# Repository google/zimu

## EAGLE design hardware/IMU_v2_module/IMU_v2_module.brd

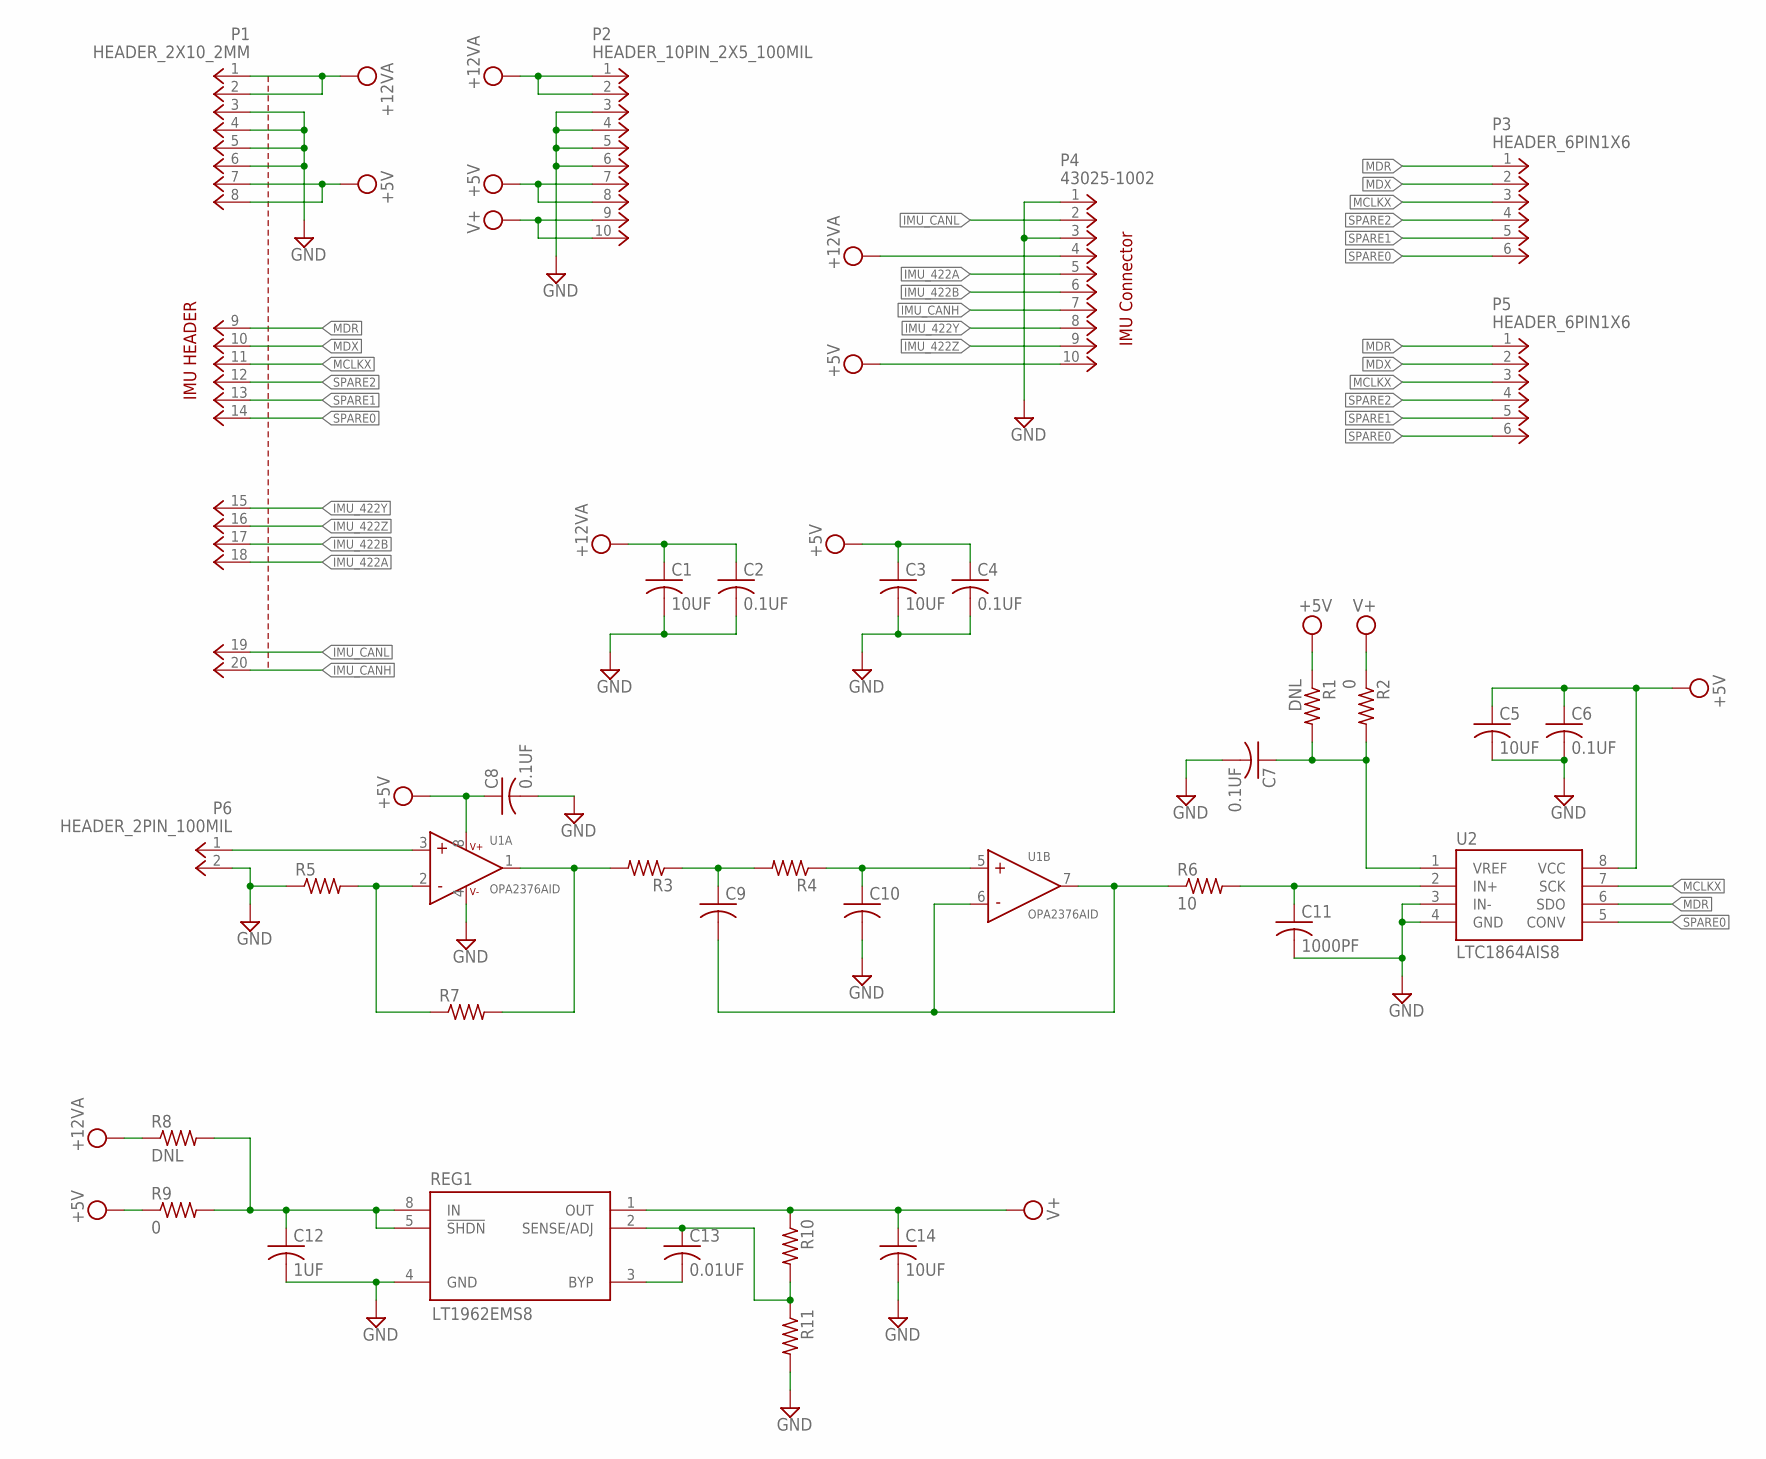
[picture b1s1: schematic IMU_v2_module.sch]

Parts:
C1, C3, C14: 10UF; C1206K
C2, C4, C6, C7, C8: 0.1UF; C0603K
C5: 10UF; C1206
C9, C10: C0603K
C11: 1000PF; C0603K
C12: 1UF; C0603K
C13: 0.01UF; C0603K
P1: HEADER_2X10_2MM
P2: HEADER_10PIN_2X5_100MIL; HEADER_2X5
P3, P5: HEADER_6PIN1X6; HEADER_1X6
P4: 43025-1002; MICRO-FIT_10RA
P6: HEADER_2PIN_100MIL; HEADER_1X2
R1, R8: DNL; R0603
R2, R9: 0; R0603
R3, R4, R5, R7: R0603
R6: 10; R0603
R10, R11: R-US_R0603; R0603
REG1: LT1962EMS8; MSOP8
U1: OPA2376AID; SOIC8
U2: LTC1864AIS8; SOIC8

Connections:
+5V: C3.1, C4.1, C5.1, C6.1, C8.1, P1.7, P1.8, P2.7, P2.8, P4.10, R1.1, R9.1, U1.8 (V+), U2.8 (VCC)
+12VA: C1.1, C2.1, P1.1, P1.2, P2.1, P2.2, P4.4, R8.1
GND: C1.2, C2.2, C3.2, C4.2, C5.2, C6.2, C7.2, C8.2, C10.2, C11.2, C12.2, C14.2, P1.3, P1.4, P1.5, P1.6, P2.3, P2.4, P2.5, P2.6, P4.1, P4.3, P6.2, R5.1, R11.2, REG1.4 (GND), U1.4 (V-), U2.3 (IN-), U2.4 (GND)
IMU_422A: P1.18, P4.5
IMU_422B: P1.17, P4.6
IMU_422Y: P1.15, P4.8
IMU_422Z: P1.16, P4.9
IMU_CANH: P1.20, P4.7
IMU_CANL: P1.19, P4.2
LC_A: C9.2, R6.1, U1.6 (IN-), U1.7 (OUT)
MCLKX: P1.11, P3.3, P5.3, U2.7 (SCK)
MDR: P1.9, P3.1, P5.1, U2.6 (SDO)
MDX: P1.10, P3.2, P5.2
unnamed: C12.1, R8.2, R9.2, REG1.5 (!SHDN), REG1.8 (IN)
unnamed: C7.1, R1.2, R2.2, U2.1 (VREF)
unnamed: R5.2, R7.1, U1.2 (IN-)
unnamed: P6.1, U1.3 (IN+)
unnamed: R3.2, R7.2, U1.1 (OUT)
unnamed: C11.1, R6.2, U2.2 (IN+)
unnamed: C9.1, R3.1, R4.2
unnamed: C10.1, R4.1, U1.5 (IN+)
unnamed: C13.2, REG1.3 (BYP)
unnamed: C13.1, R10.2, R11.1, REG1.2 (SENSE/ADJ)
SPARE0: P1.14, P3.6, P5.6, U2.5 (CONV)
SPARE1: P1.13, P3.5, P5.5
SPARE2: P1.12, P3.4, P5.4
V+: C14.1, P2.9, P2.10, R2.1, R10.1, REG1.1 (OUT)

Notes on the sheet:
IMU HEADER
IMU Connector

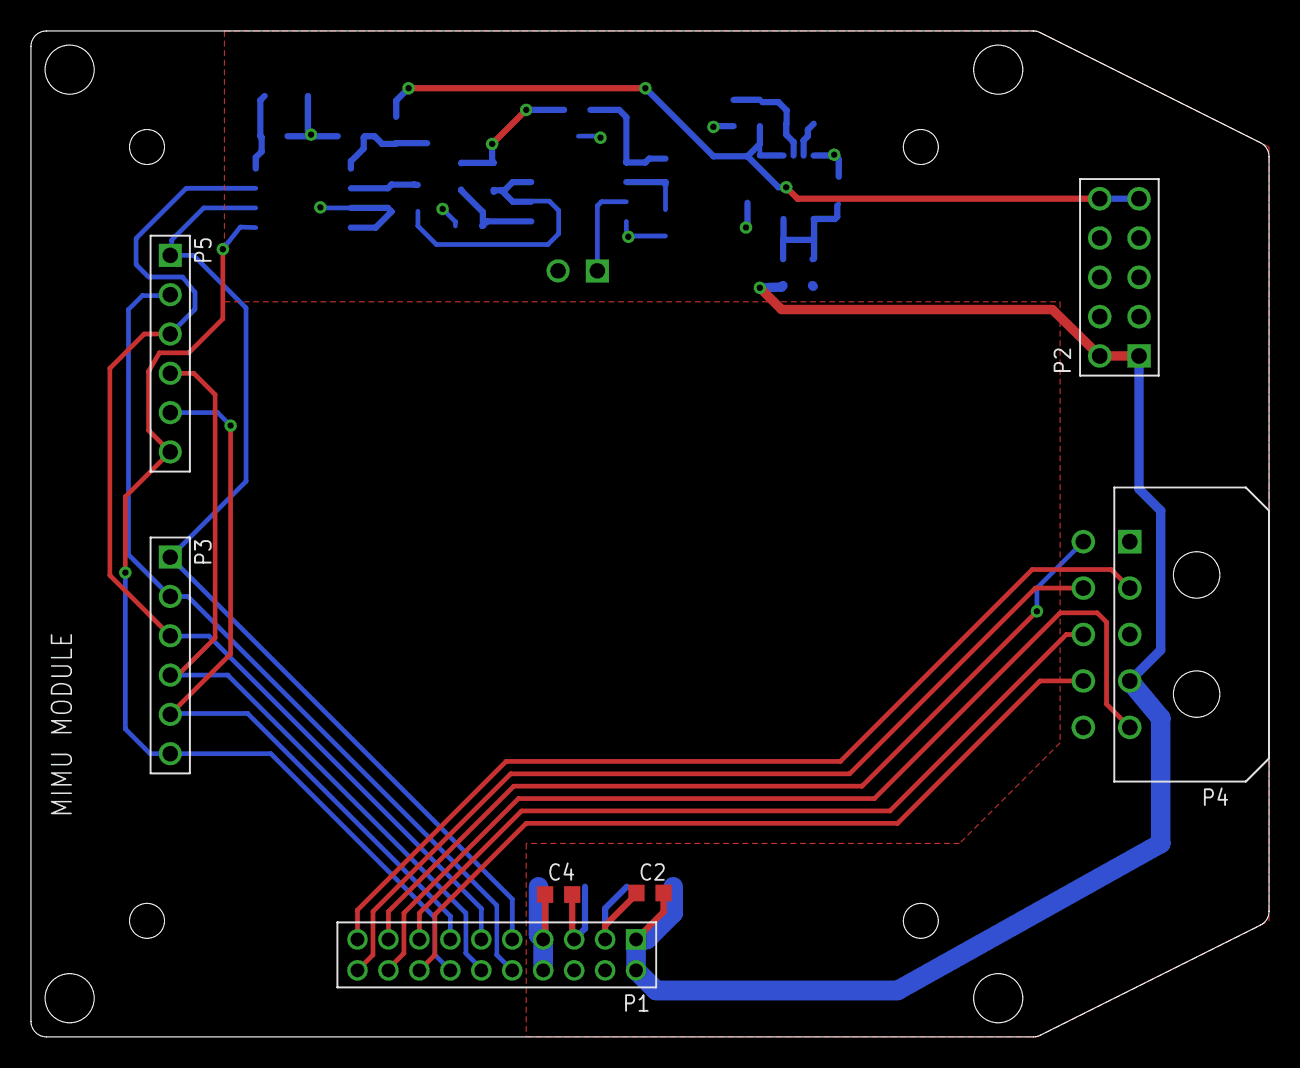
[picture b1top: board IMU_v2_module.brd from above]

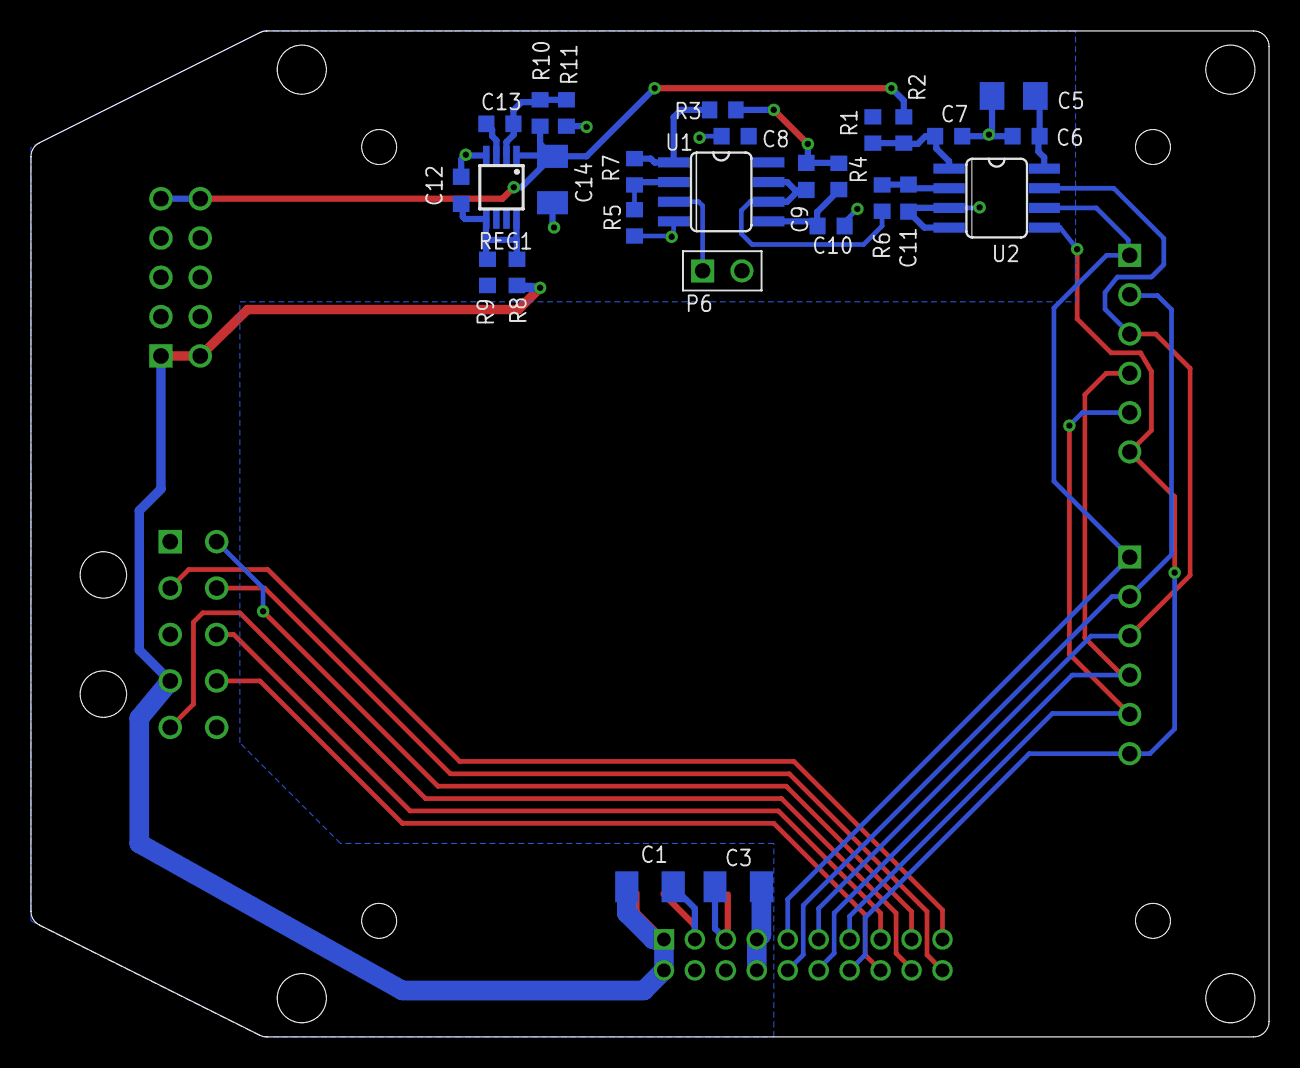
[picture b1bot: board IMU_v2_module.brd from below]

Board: 2 copper layers, 80.0 x 65.0 mm, 34 parts (27 on the bottom side), 27 nets.

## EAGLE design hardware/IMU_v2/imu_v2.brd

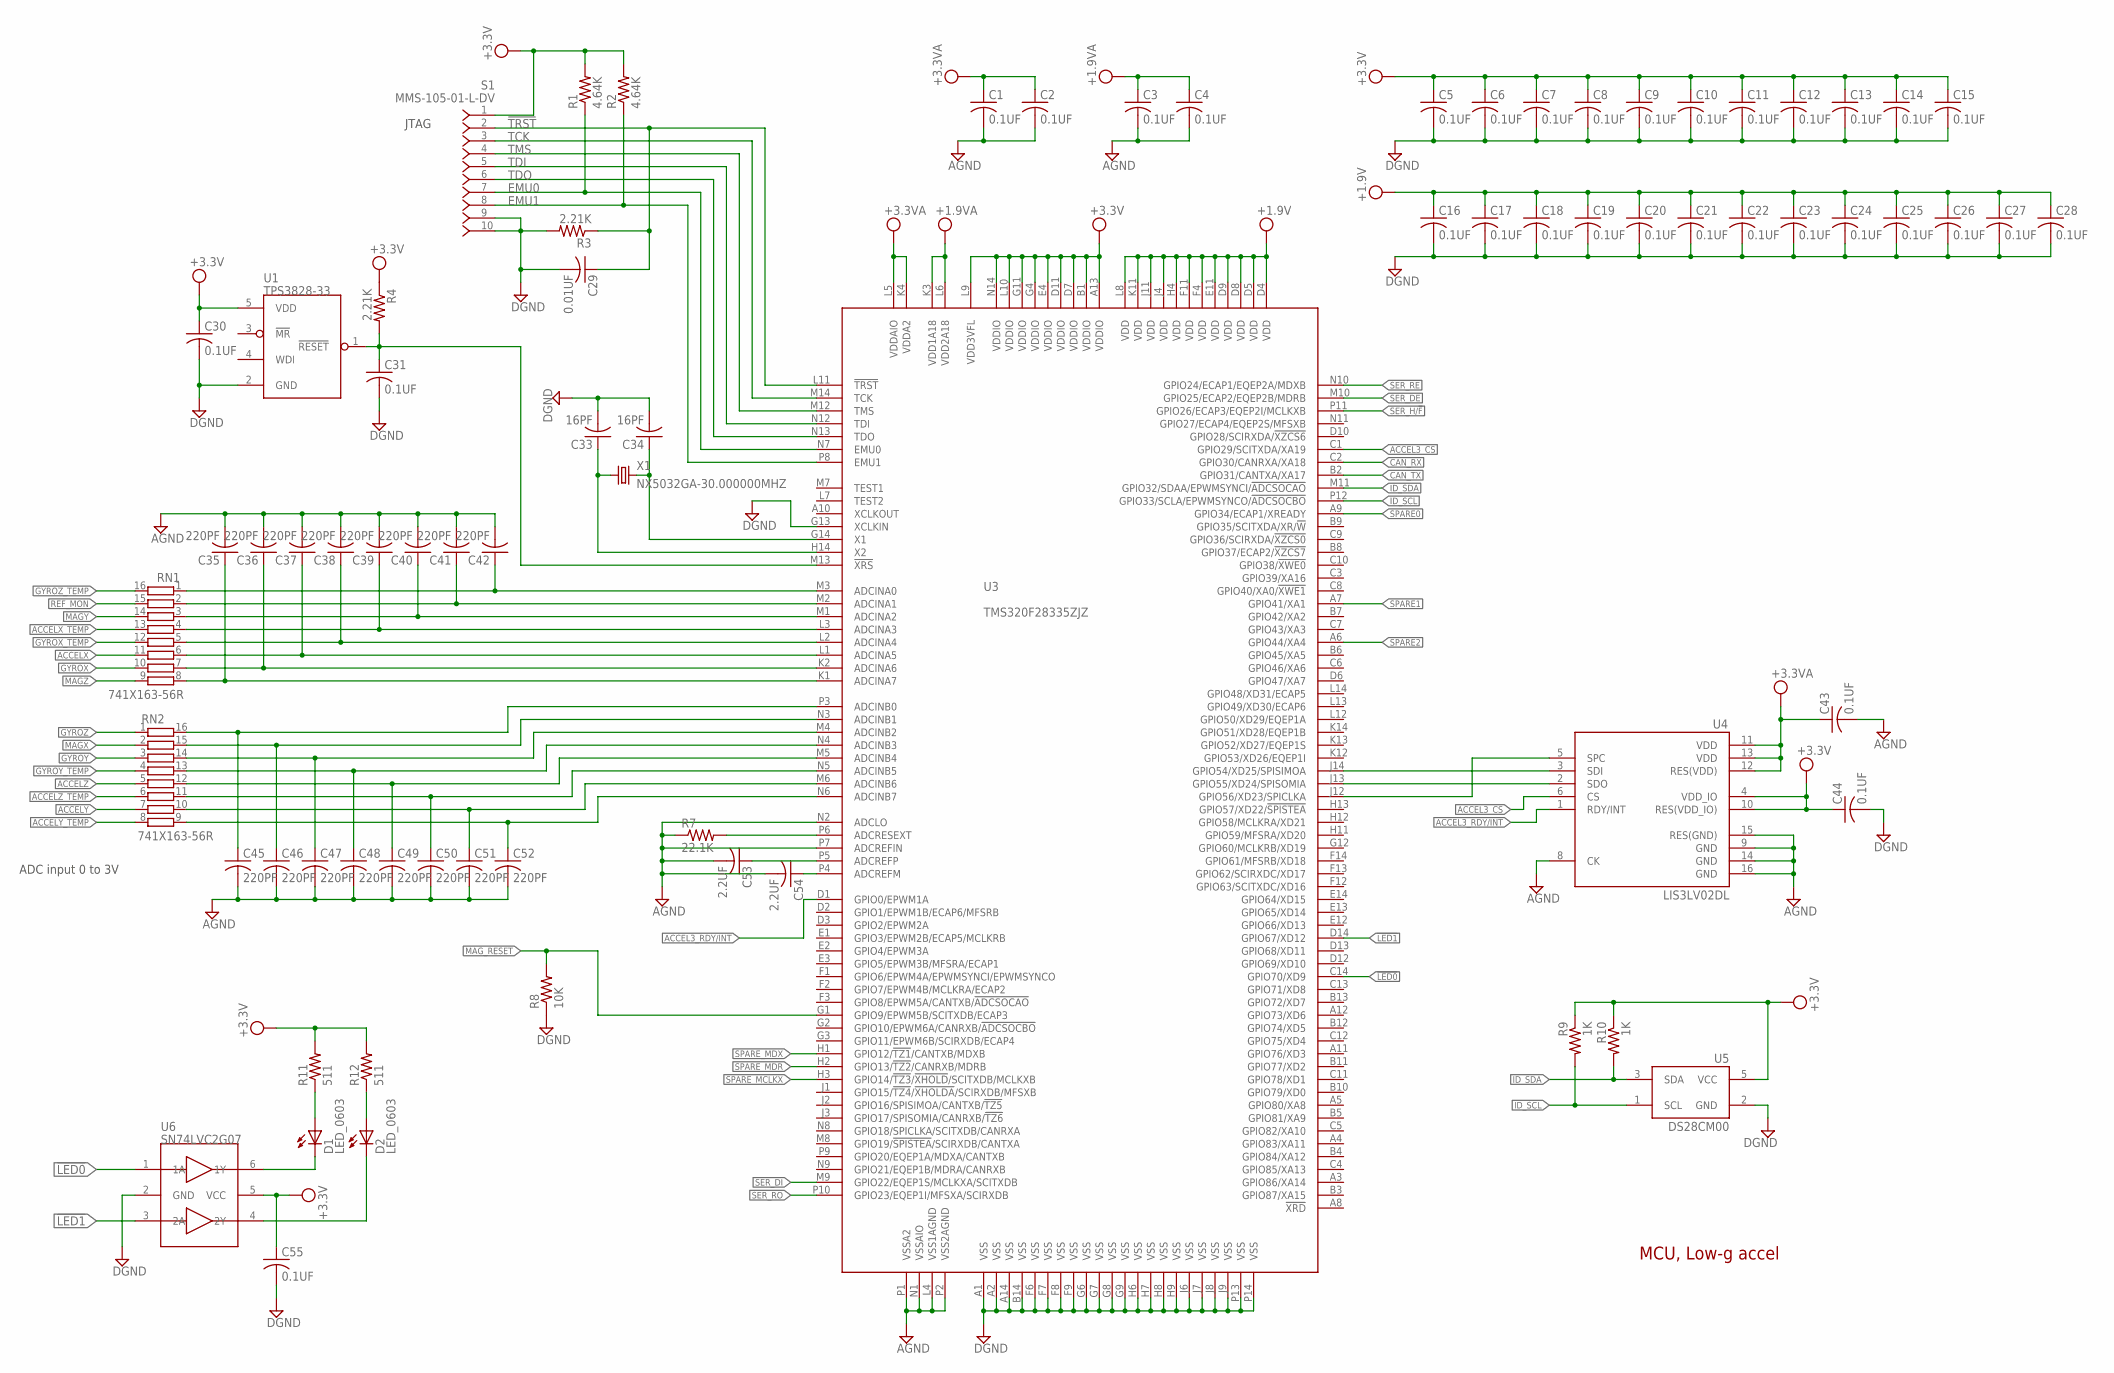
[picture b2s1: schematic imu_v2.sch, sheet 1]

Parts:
C1, C2, C3, C4, C5, C6, C7, C8, C9, C10, C11, C12, C13, C14, C15, C16, C17, C18, C19, C20, C21, C22, C23, C24, C25, C26, C27, C28, C30, C31, C43, C44, C55: 0.1UF; C0603K
C29: 0.01UF; C0603K
C33, C34: 16PF; C0603K
C35, C36, C37, C38, C39, C40, C41, C42, C45, C46, C47, C48, C49, C50, C51, C52: 220PF; C0603K
C53, C54: 2.2UF; C0603K
D1, D2: LED_0603
R1, R2: 4.64K; R0603
R3, R4: 2.21K; R0603
R7: 22.1K; R0603
R8: 10K; R0603
R9, R10: 1K; R0603
R11, R12: 511; R0603
RN1, RN2: 741X163-56R; 741X163
S1: MMS-105-01-L-DV; HEADER_2X5_2MM_TH
U1: TPS3828-33; SOT23-5
U3: TMS320F28335ZJZ; ZJZ_PBGA176
U4: LIS3LV02DL; LIS3LV02DL_LGA16
U5: DS28CM00; SOT23-5L
U6: SN74LVC2G07; SOT23-6
X1: NX5032GA-30.000000MHZ; NX5032GA

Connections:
!LED0: U3.C14 (GPIO70/XD9), U6.1 (1A)
!LED1: U3.D14 (GPIO67/XD12), U6.3 (2A)
!TRST: C29.1, R3.1, S1.2 (1), U3.L11 (!TRST!)
+1.9V: C16.1, C17.1, C18.1, C19.1, C20.1, C21.1, C22.1, C23.1, C24.1, C25.1, C26.1, C27.1, C28.1, U3.D4 (VDD), U3.D5 (VDD), U3.D8 (VDD), U3.D9 (VDD), U3.E11 (VDD), U3.F4 (VDD), U3.F11 (VDD), U3.H4 (VDD), U3.J4 (VDD), U3.J11 (VDD), U3.K11 (VDD), U3.L8 (VDD); also elsewhere on the board
+1.9VA: C3.1, C4.1, U3.K3 (VDD1A18), U3.L6 (VDD2A18); also elsewhere on the board
+3.3V: C5.1, C6.1, C7.1, C8.1, C9.1, C10.1, C11.1, C12.1, C13.1, C14.1, C15.1, C30.1, C44.1, C55.1, R1.2, R2.2, R4.1, R9.1, R10.1, R11.2, R12.2, S1.1, U1.5 (VDD), U3.A13 (VDDIO), U3.B1 (VDDIO), U3.D7 (VDDIO), U3.D11 (VDDIO), U3.E4 (VDDIO), U3.G4 (VDDIO), U3.G11 (VDDIO), U3.L9 (VDD3VFL), U3.L10 (VDDIO), U3.N14 (VDDIO), U4.4 (VDD_IO), U4.10 (RES(VDD_IO)), U5.5 (VCC), U6.5 (VCC); also elsewhere on the board
+3.3VA: C1.1, C2.1, C43.1, U3.K4 (VDDA2), U3.L5 (VDDAIO), U4.11 (VDD), U4.12 (RES(VDD)), U4.13 (VDD); also elsewhere on the board
ACCEL3_CLK: U3.J12 (GPIO56/XD23/SPICLKA), U4.5 (SPC)
ACCEL3_CS: U3.C1 (GPIO29/SCITXDA/XA19), U4.6 (CS)
ACCEL3_RDY/INT: U3.D1 (GPIO0/EPWM1A), U4.1 (RDY/INT)
ACCEL3_SIMO: U3.J14 (GPIO54/XD25/SPISIMOA), U4.3 (SDI)
ACCEL3_SOMI: U3.J13 (GPIO55/XD24/SPISOMIA), U4.2 (SDO)
ACCELX: RN1.11; also elsewhere on the board
ACCELX_TEMP: RN1.13; also elsewhere on the board
ACCELY: RN2.7; also elsewhere on the board
ACCELY_TEMP: RN2.8; also elsewhere on the board
ACCELZ: RN2.5; also elsewhere on the board
ACCELZ_TEMP: RN2.6; also elsewhere on the board
AGND: C1.2, C2.2, C3.2, C4.2, C35.2, C36.2, C37.2, C38.2, C39.2, C40.2, C41.2, C42.2, C43.2, C45.2, C46.2, C47.2, C48.2, C49.2, C50.2, C51.2, C52.2, C53.2, C54.2, R7.1, U3.L4 (VSS1AGND), U3.N1 (VSSAIO), U3.N2 (ADCLO), U3.P1 (VSSA2), U3.P2 (VSS2AGND), U3.P7 (ADCREFIN), U4.8 (CK), U4.9 (GND), U4.14 (GND), U4.15 (RES(GND)), U4.16 (GND); also elsewhere on the board
CAN_RX: U3.C2 (GPIO30/CANRXA/XA18); also elsewhere on the board
CAN_TX: U3.B2 (GPIO31/CANTXA/XA17); also elsewhere on the board
DGND: C5.2, C6.2, C7.2, C8.2, C9.2, C10.2, C11.2, C12.2, C13.2, C14.2, C15.2, C16.2, C17.2, C18.2, C19.2, C20.2, C21.2, C22.2, C23.2, C24.2, C25.2, C26.2, C27.2, C28.2, C29.2, C30.2, C31.2, C33.2, C34.2, C44.2, C55.2, R3.2, R8.1, S1.9 (1), S1.10 (1), U1.2 (GND), U3.A1 (VSS), U3.A2 (VSS), U3.A14 (VSS), U3.B14 (VSS), U3.F6 (VSS), U3.F7 (VSS), U3.F8 (VSS), U3.F9 (VSS), U3.G6 (VSS), U3.G7 (VSS), U3.G8 (VSS), U3.G9 (VSS), U3.G13 (XCLKIN), U3.H6 (VSS), U3.H7 (VSS), U3.H8 (VSS), U3.H9 (VSS), U3.J6 (VSS), U3.J7 (VSS), U3.J8 (VSS), U3.J9 (VSS), U3.P13 (VSS), U3.P14 (VSS), U5.2 (GND), U6.2 (GND); also elsewhere on the board
EMU0: R1.1, S1.7 (1), U3.N7 (EMU0)
EMU1: R2.1, S1.8 (1), U3.P8 (EMU1)
GYROX: RN1.10; also elsewhere on the board
GYROX_TEMP: RN1.12; also elsewhere on the board
GYROY: RN2.3; also elsewhere on the board
GYROY_TEMP: RN2.4; also elsewhere on the board
GYROZ: RN2.1; also elsewhere on the board
GYROZ_TEMP: RN1.16; also elsewhere on the board
ID_SCL: R9.2, U3.P12 (GPIO33/SCLA/EPWMSYNCO/!ADCSOCBO!), U5.1 (SCL)
ID_SDA: R10.2, U3.M11 (GPIO32/SDAA/EPWMSYNCI/!ADCSOCAO!), U5.3 (SDA)
MAGX: RN2.2; also elsewhere on the board
MAGY: RN1.14; also elsewhere on the board
MAGZ: RN1.9; also elsewhere on the board
MAG_RESET: R8.2, U3.G1 (GPIO9/EPWM5B/SCITXDB/ECAP3); also elsewhere on the board
unnamed: C42.1, RN1.1, U3.M3 (ADCINA0)
unnamed: C41.1, RN1.2, U3.M2 (ADCINA1)
unnamed: C40.1, RN1.3, U3.M1 (ADCINA2)
unnamed: C39.1, RN1.4, U3.L3 (ADCINA3)
unnamed: C38.1, RN1.5, U3.L2 (ADCINA4)
unnamed: C37.1, RN1.6, U3.L1 (ADCINA5)
unnamed: C36.1, RN1.7, U3.K2 (ADCINA6)
unnamed: C35.1, RN1.8, U3.K1 (ADCINA7)
unnamed: C45.1, RN2.16, U3.P3 (ADCINB0)
unnamed: C46.1, RN2.15, U3.N3 (ADCINB1)
unnamed: C47.1, RN2.14, U3.M4 (ADCINB2)
unnamed: C48.1, RN2.13, U3.N4 (ADCINB3)
unnamed: C49.1, RN2.12, U3.M5 (ADCINB4)
unnamed: C50.1, RN2.11, U3.N5 (ADCINB5)
unnamed: C51.1, RN2.10, U3.M6 (ADCINB6)
unnamed: C52.1, RN2.9, U3.N6 (ADCINB7)
unnamed: C31.1, R4.2, U1.1 (!RESET), U3.M13 (!XRS!)
unnamed: C33.1, U3.H14 (X2), X1.1
unnamed: C34.1, U3.G14 (X1), X1.2
unnamed: R7.2, U3.P6 (ADCRESEXT)
unnamed: C54.1, U3.P4 (ADCREFM)
unnamed: C53.1, U3.P5 (ADCREFP)
unnamed: D1.A, R11.1
unnamed: D2.A, R12.1
unnamed: D1.C, U6.6 (1Y)
unnamed: D2.C, U6.4 (2Y)
REF_MON: RN1.15; also elsewhere on the board
SER_!RE: U3.N10 (GPIO24/ECAP1/EQEP2A/MDXB); also elsewhere on the board
SER_DE: U3.M10 (GPIO25/ECAP2/EQEP2B/MDRB); also elsewhere on the board
SER_DI: U3.M9 (GPIO22/EQEP1S/MCLKXA/SCITXDB); also elsewhere on the board
SER_H/!F: U3.P11 (GPIO26/ECAP3/EQEP2I/MCLKXB); also elsewhere on the board
SER_RO: U3.P10 (GPIO23/EQEP1I/MFSXA/SCIRXDB); also elsewhere on the board
SPARE0: U3.A9 (GPIO34/ECAP1/XREADY); also elsewhere on the board
SPARE1: U3.A7 (GPIO41/XA1); also elsewhere on the board
SPARE2: U3.A6 (GPIO44/XA4); also elsewhere on the board
SPARE_MCLKX: U3.H3 (GPIO14/!TZ3!/!XHOLD!/SCITXDB/MCLKXB); also elsewhere on the board
SPARE_MDR: U3.H2 (GPIO13/!TZ2!/CANRXB/MDRB); also elsewhere on the board
SPARE_MDX: U3.H1 (GPIO12/!TZ1!/CANTXB/MDXB); also elsewhere on the board
TCK: S1.3 (1), U3.M14 (TCK)
TDI: S1.5 (1), U3.N12 (TDI)
TDO: S1.6 (1), U3.N13 (TDO)
TMS: S1.4 (1), U3.M12 (TMS)

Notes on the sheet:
JTAG
MCU, Low-g accel
ADC input 0 to 3V

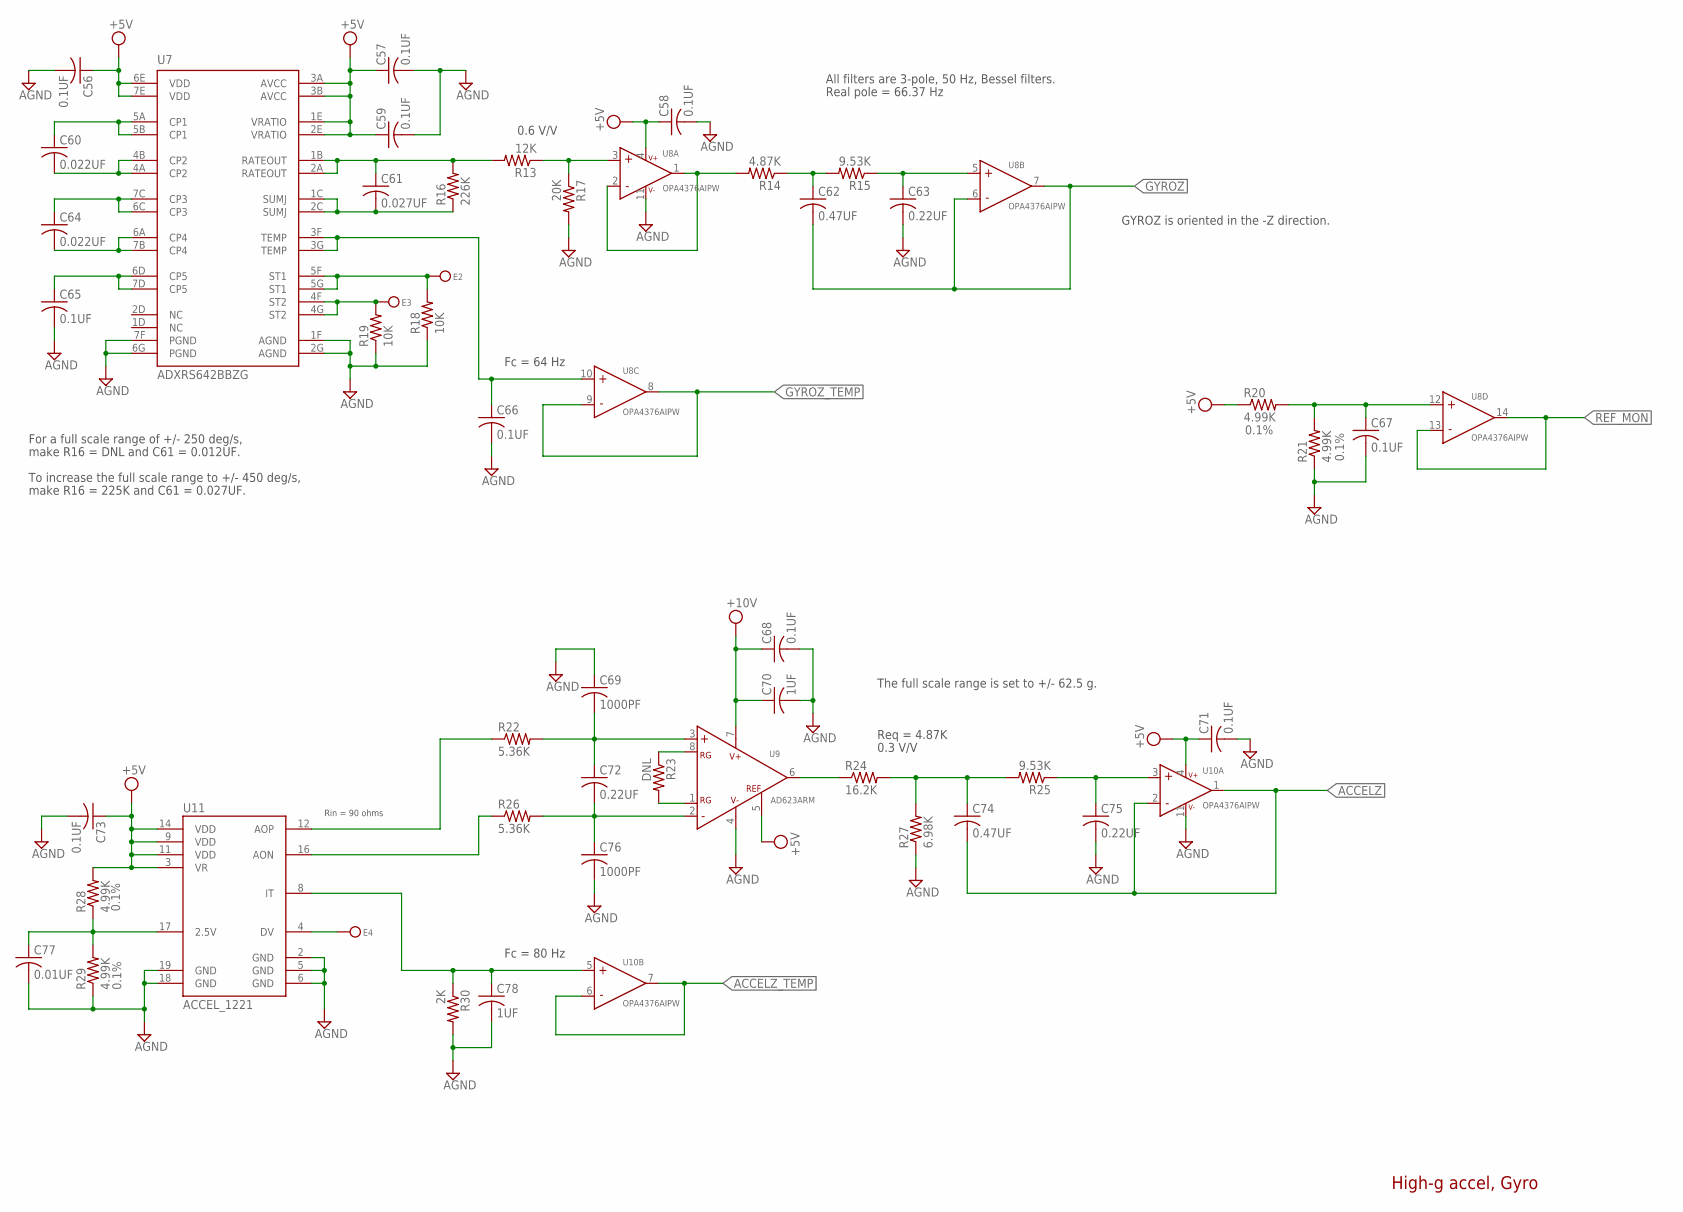
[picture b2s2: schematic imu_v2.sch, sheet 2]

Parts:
C56, C57, C58, C59, C65, C66, C67, C68, C71, C73: 0.1UF; C0603K
C60, C64: 0.022UF; C0603K
C61: 0.027UF; C0603K
C62, C74: 0.47UF; C0603K
C63, C72, C75: 0.22UF; C0603K
C69, C76: 1000PF; C0603K
C70, C78: 1UF; C0603K
C77: 0.01UF; C0603K
E2, E3, E4: TP30
R13: 12K; R0603
R14: 4.87K; R0603
R15, R25: 9.53K; R0603
R16: 226K; R0603
R17: 20K; R0603
R18, R19: 10K; R0603
R20, R21, R28, R29: 4.99K; R0603
R22, R26: 5.36K; R0603
R23: DNL; R0603
R24: 16.2K; R0603
R27: 6.98K; R0603
R30: 2K; R0603
U7: ADXRS642BBZG; ADXRS_CBGA32
U8, U10: OPA4376AIPW; TSSOP14
U9: AD623ARM; MSOP8
U11: ACCEL_1221; 1221_LCC

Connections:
+5V: C56.1, C57.1, C58.1, C59.1, C71.1, C73.1, R20.1, R28.2, U7.1E (VRATIO), U7.2E (VRATIO), U7.3A (AVCC), U7.3B (AVCC), U7.6E (VDD), U7.7E (VDD), U8.4 (V+), U9.5 (REF), U10.4 (V+), U11.3 (VR), U11.9 (VDD), U11.11 (VDD), U11.14 (VDD); also elsewhere on the board
+10V: C68.1, C70.1, U9.7 (VS+); also elsewhere on the board
ACCELZ: C74.2, U10.1 (OUT), U10.2 (IN-); also elsewhere on the board
ACCELZ_TEMP: U10.6 (IN-), U10.7 (OUT); also elsewhere on the board
AGND: C56.2, C57.2, C58.2, C59.2, C63.2, C65.2, C66.2, C67.2, C68.2, C69.1, C70.2, C71.2, C73.2, C75.2, C76.2, C77.2, C78.2, R17.2, R18.1, R19.1, R21.1, R27.1, R29.1, R30.2, U7.1F (AGND), U7.2G (AGND), U7.6G (PGND), U7.7F (PGND), U8.11 (V-), U9.4 (VS-), U10.11 (V-), U11.2 (GND), U11.5 (GND), U11.6 (GND), U11.18 (GND), U11.19 (GND); also elsewhere on the board
GYROZ: C62.2, U8.6 (IN-), U8.7 (OUT); also elsewhere on the board
GYROZ_TEMP: U8.8 (OUT), U8.9 (IN-); also elsewhere on the board
unnamed: C60.1, U7.5A (CP1), U7.5B (CP1)
unnamed: C60.2, U7.4A (CP2), U7.4B (CP2)
unnamed: C64.1, U7.6C (CP3), U7.7C (CP3)
unnamed: C64.2, U7.6A (CP4), U7.7B (CP4)
unnamed: C65.1, U7.6D (CP5), U7.7D (CP5)
unnamed: C77.1, R28.1, R29.2, U11.17 (2.5V)
unnamed: C61.2, R16.1, U7.1C (SUMJ), U7.2C (SUMJ)
unnamed: E4.1, U11.4 (DV)
unnamed: C61.1, R13.2, R16.2, U7.1B (RATEOUT), U7.2A (RATEOUT)
unnamed: C66.1, U7.3F (TEMP), U7.3G (TEMP), U8.10 (IN+)
unnamed: C78.1, R30.1, U10.5 (IN+), U11.8 (IT)
unnamed: R22.1, U11.12 (AOP)
unnamed: R26.1, U11.16 (AON)
unnamed: R13.1, R17.1, U8.3 (IN+)
unnamed: R14.2, U8.1 (OUT), U8.2 (IN-)
unnamed: C62.1, R14.1, R15.2
unnamed: C63.1, R15.1, U8.5 (IN+)
unnamed: C69.2, C72.1, R22.2, U9.3 (IN+)
unnamed: C72.2, C76.1, R26.2, U9.2 (IN-)
unnamed: C67.1, R20.2, R21.2, U8.12 (IN+)
unnamed: R23.1, U9.8 (RG)
unnamed: R23.2, U9.1 (RG)
unnamed: R24.1, U9.6 (VOUT)
unnamed: C74.1, R24.2, R25.2, R27.2
unnamed: C75.1, R25.1, U10.3 (IN+)
unnamed: E2.1, R18.2, U7.5F (ST1), U7.5G (ST1)
unnamed: E3.1, R19.2, U7.4F (ST2), U7.4G (ST2)
REF_MON: U8.13 (IN-), U8.14 (OUT); also elsewhere on the board

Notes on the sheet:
0.3 V/V
Rin = 90 ohms
All filters are 3-pole, 50 Hz, Bessel filters.
Real pole = 66.37 Hz
Fc = 64 Hz
0.6 V/V
Req = 4.87K
Fc = 80 Hz
The full scale range is set to +/- 62.5 g.
GYROZ is oriented in the -Z direction.
For a full scale range of +/- 250 deg/s,
make R16 = DNL and C61 = 0.012UF.
make R16 = 225K and C61 = 0.027UF.
To increase the full scale range to +/- 450 deg/s,
High-g accel, Gyro

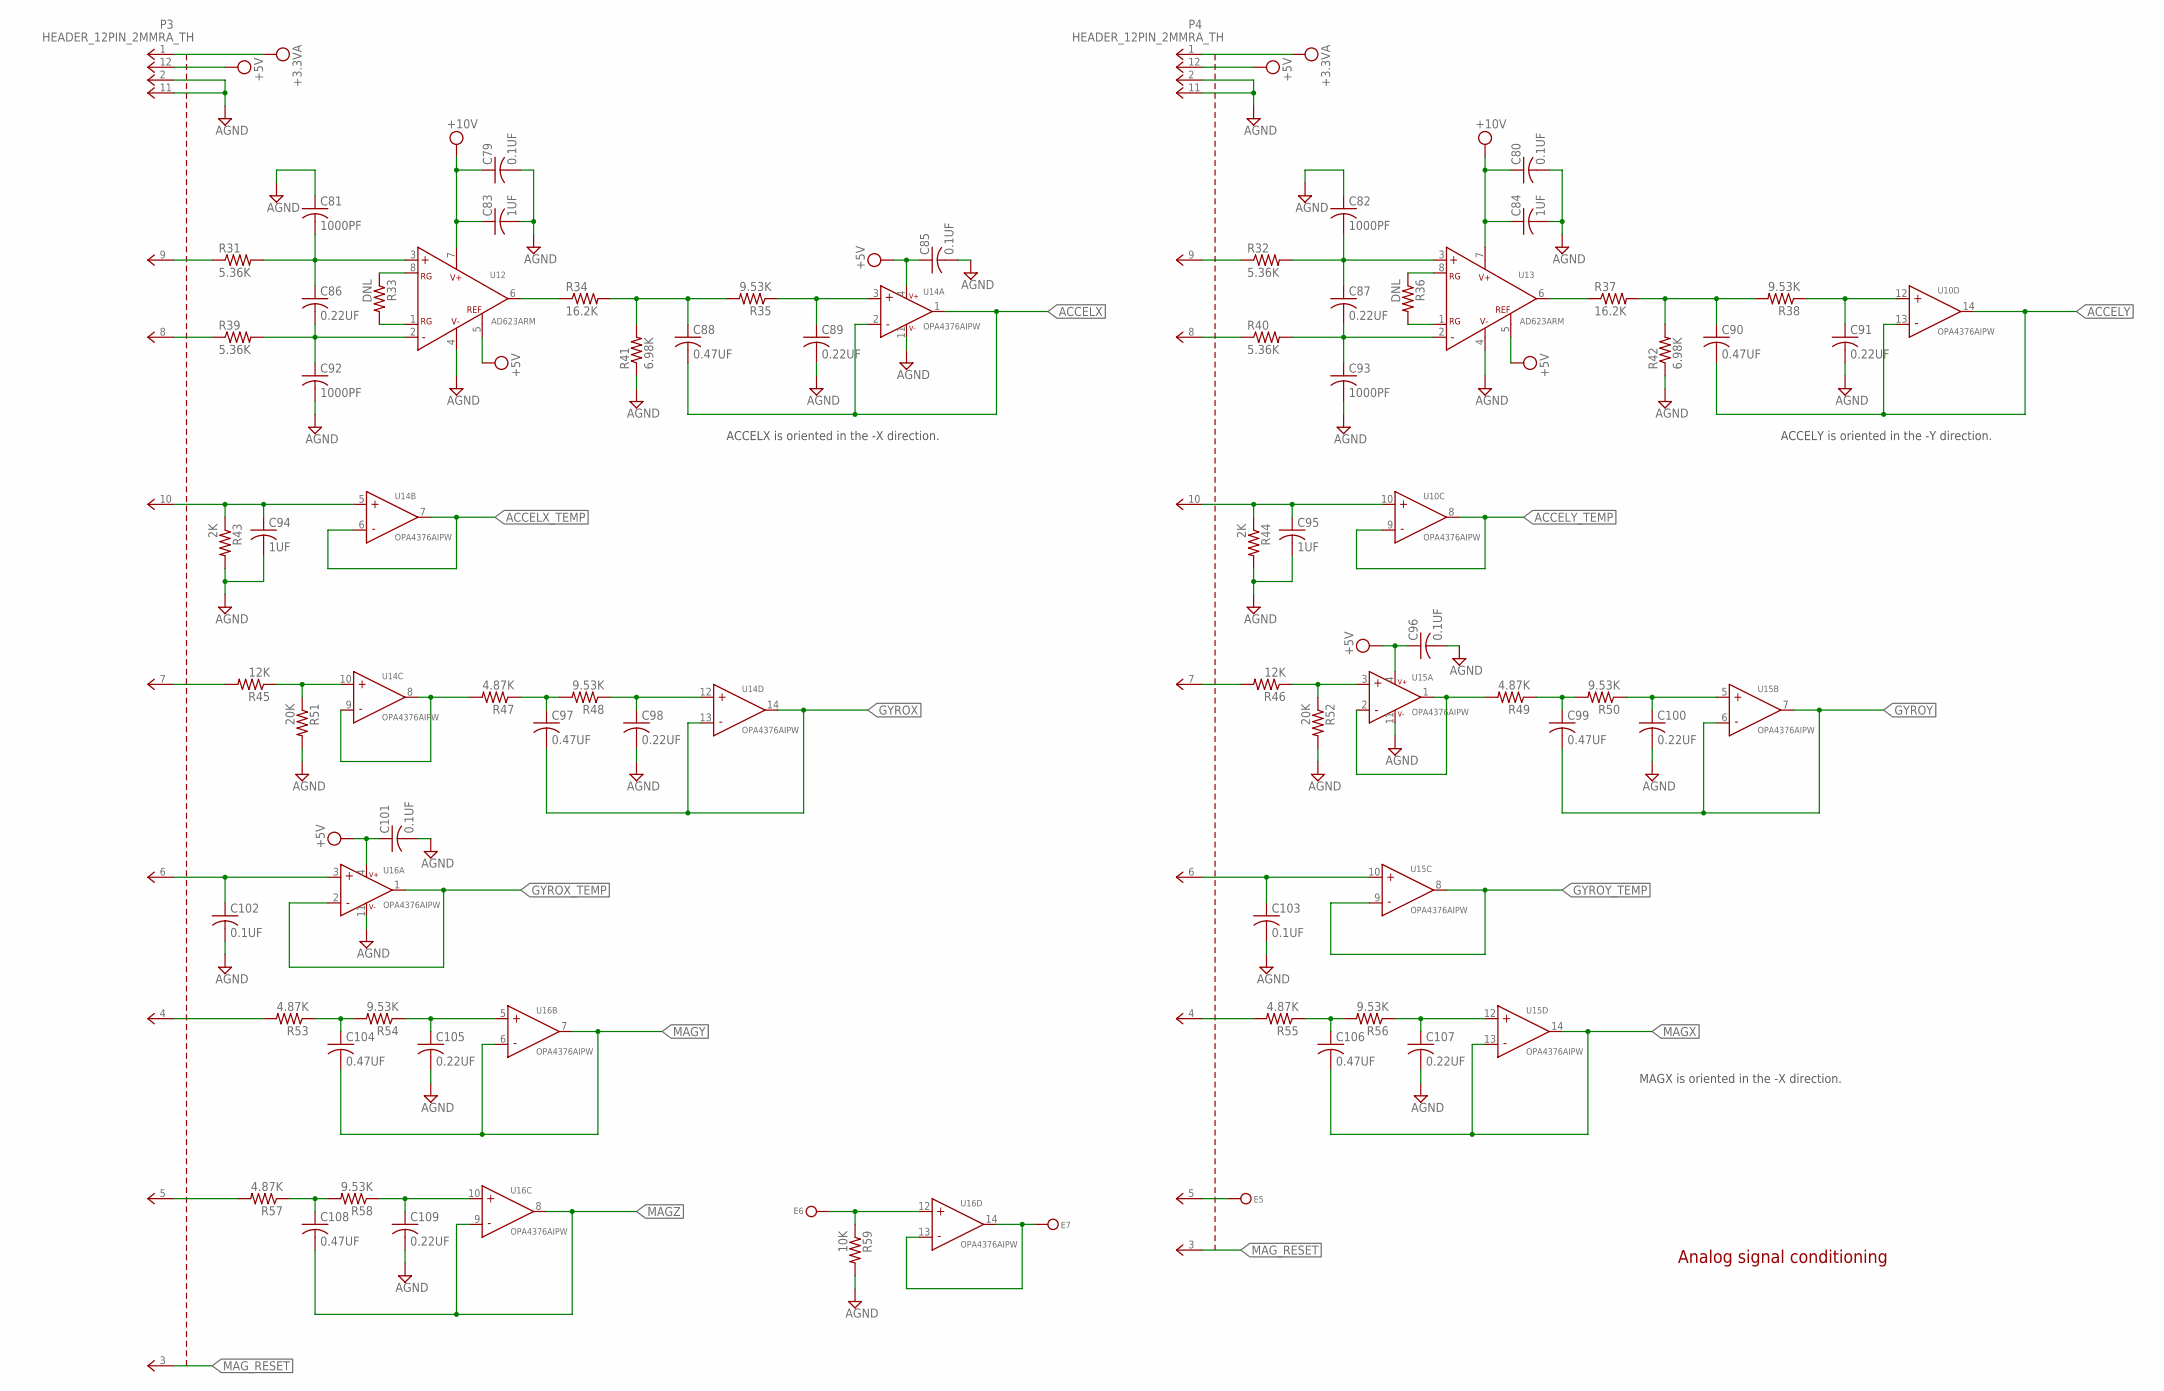
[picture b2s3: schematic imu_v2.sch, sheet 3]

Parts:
C79, C80, C85, C96, C101, C102, C103: 0.1UF; C0603K
C81, C82, C92, C93: 1000PF; C0603K
C83, C84, C94, C95: 1UF; C0603K
C86, C87, C89, C91, C98, C100, C105, C107, C109: 0.22UF; C0603K
C88, C90, C97, C99, C104, C106, C108: 0.47UF; C0603K
E5, E6, E7: TP30
P3, P4: HEADER_12PIN_2MMRA_TH; TMM-112-01-T-S-RA
R31, R32, R39, R40: 5.36K; R0603
R33, R36: DNL; R0603
R34, R37: 16.2K; R0603
R35, R38, R48, R50, R54, R56, R58: 9.53K; R0603
R41, R42: 6.98K; R0603
R43, R44: 2K; R0603
R45, R46: 12K; R0603
R47, R49, R53, R55, R57: 4.87K; R0603
R51, R52: 20K; R0603
R59: 10K; R0603
U10, U14, U15, U16: OPA4376AIPW; TSSOP14
U12, U13: AD623ARM; MSOP8

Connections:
+3.3VA: P3.1, P4.1; also elsewhere on the board
+5V: C85.1, C96.1, C101.1, P3.12, P4.12, U12.5 (REF), U13.5 (REF), U14.4 (V+), U15.4 (V+), U16.4 (V+); also elsewhere on the board
+10V: C79.1, C80.1, C83.1, C84.1, U12.7 (VS+), U13.7 (VS+); also elsewhere on the board
ACCELX: C88.2, U14.1 (OUT), U14.2 (IN-); also elsewhere on the board
ACCELX_TEMP: U14.6 (IN-), U14.7 (OUT); also elsewhere on the board
ACCELY: C90.2, U10.13 (IN-), U10.14 (OUT); also elsewhere on the board
ACCELY_TEMP: U10.8 (OUT), U10.9 (IN-); also elsewhere on the board
AGND: C79.2, C80.2, C81.1, C82.1, C83.2, C84.2, C85.2, C89.2, C91.2, C92.2, C93.2, C94.2, C95.2, C96.2, C98.2, C100.2, C101.2, C102.2, C103.2, C105.2, C107.2, C109.2, P3.2, P3.11, P4.2, P4.11, R41.1, R42.1, R43.2, R44.2, R51.2, R52.2, R59.2, U12.4 (VS-), U13.4 (VS-), U14.11 (V-), U15.11 (V-), U16.11 (V-); also elsewhere on the board
GYROX: C97.2, U14.13 (IN-), U14.14 (OUT); also elsewhere on the board
GYROX_TEMP: U16.1 (OUT), U16.2 (IN-); also elsewhere on the board
GYROY: C99.2, U15.6 (IN-), U15.7 (OUT); also elsewhere on the board
GYROY_TEMP: U15.8 (OUT), U15.9 (IN-); also elsewhere on the board
MAGX: C106.2, U15.13 (IN-), U15.14 (OUT); also elsewhere on the board
MAGY: C104.2, U16.6 (IN-), U16.7 (OUT); also elsewhere on the board
MAGZ: C108.2, U16.8 (OUT), U16.9 (IN-); also elsewhere on the board
MAG_RESET: P3.3, P4.3; also elsewhere on the board
unnamed: E7.1, U16.13 (IN-), U16.14 (OUT)
unnamed: E6.1, R59.1, U16.12 (IN+)
unnamed: E5.1, P4.5
unnamed: P3.7, R45.2
unnamed: R45.1, R51.1, U14.10 (IN+)
unnamed: R47.2, U14.8 (OUT), U14.9 (IN-)
unnamed: C97.1, R47.1, R48.2
unnamed: C98.1, R48.1, U14.12 (IN+)
unnamed: P4.7, R46.2
unnamed: R46.1, R52.1, U15.3 (IN+)
unnamed: R49.2, U15.1 (OUT), U15.2 (IN-)
unnamed: C99.1, R49.1, R50.2
unnamed: C100.1, R50.1, U15.5 (IN+)
unnamed: C103.1, P4.6, U15.10 (IN+)
unnamed: C102.1, P3.6, U16.3 (IN+)
unnamed: C95.1, P4.10, R44.1, U10.10 (IN+)
unnamed: P3.4, R53.2
unnamed: P4.9, R32.1
unnamed: C82.2, C87.1, R32.2, U13.3 (IN+)
unnamed: C87.2, C93.1, R40.2, U13.2 (IN-)
unnamed: R36.1, U13.8 (RG)
unnamed: R36.2, U13.1 (RG)
unnamed: R37.1, U13.6 (VOUT)
unnamed: C90.1, R37.2, R38.2, R42.2
unnamed: C91.1, R38.1, U10.12 (IN+)
unnamed: C94.1, P3.10, R43.1, U14.5 (IN+)
unnamed: P3.9, R31.1
unnamed: P3.8, R39.1
unnamed: C81.2, C86.1, R31.2, U12.3 (IN+)
unnamed: C86.2, C92.1, R39.2, U12.2 (IN-)
unnamed: R33.1, U12.8 (RG)
unnamed: R33.2, U12.1 (RG)
unnamed: R34.1, U12.6 (VOUT)
unnamed: C88.1, R34.2, R35.2, R41.2
unnamed: C89.1, R35.1, U14.3 (IN+)
unnamed: P4.8, R40.1
unnamed: C104.1, R53.1, R54.2
unnamed: C105.1, R54.1, U16.5 (IN+)
unnamed: P3.5, R57.2
unnamed: C108.1, R57.1, R58.2
unnamed: C109.1, R58.1, U16.10 (IN+)
unnamed: P4.4, R55.2
unnamed: C106.1, R55.1, R56.2
unnamed: C107.1, R56.1, U15.12 (IN+)

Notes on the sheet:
MAGX is oriented in the -X direction.
ACCELX is oriented in the -X direction.
ACCELY is oriented in the -Y direction.
Analog signal conditioning
